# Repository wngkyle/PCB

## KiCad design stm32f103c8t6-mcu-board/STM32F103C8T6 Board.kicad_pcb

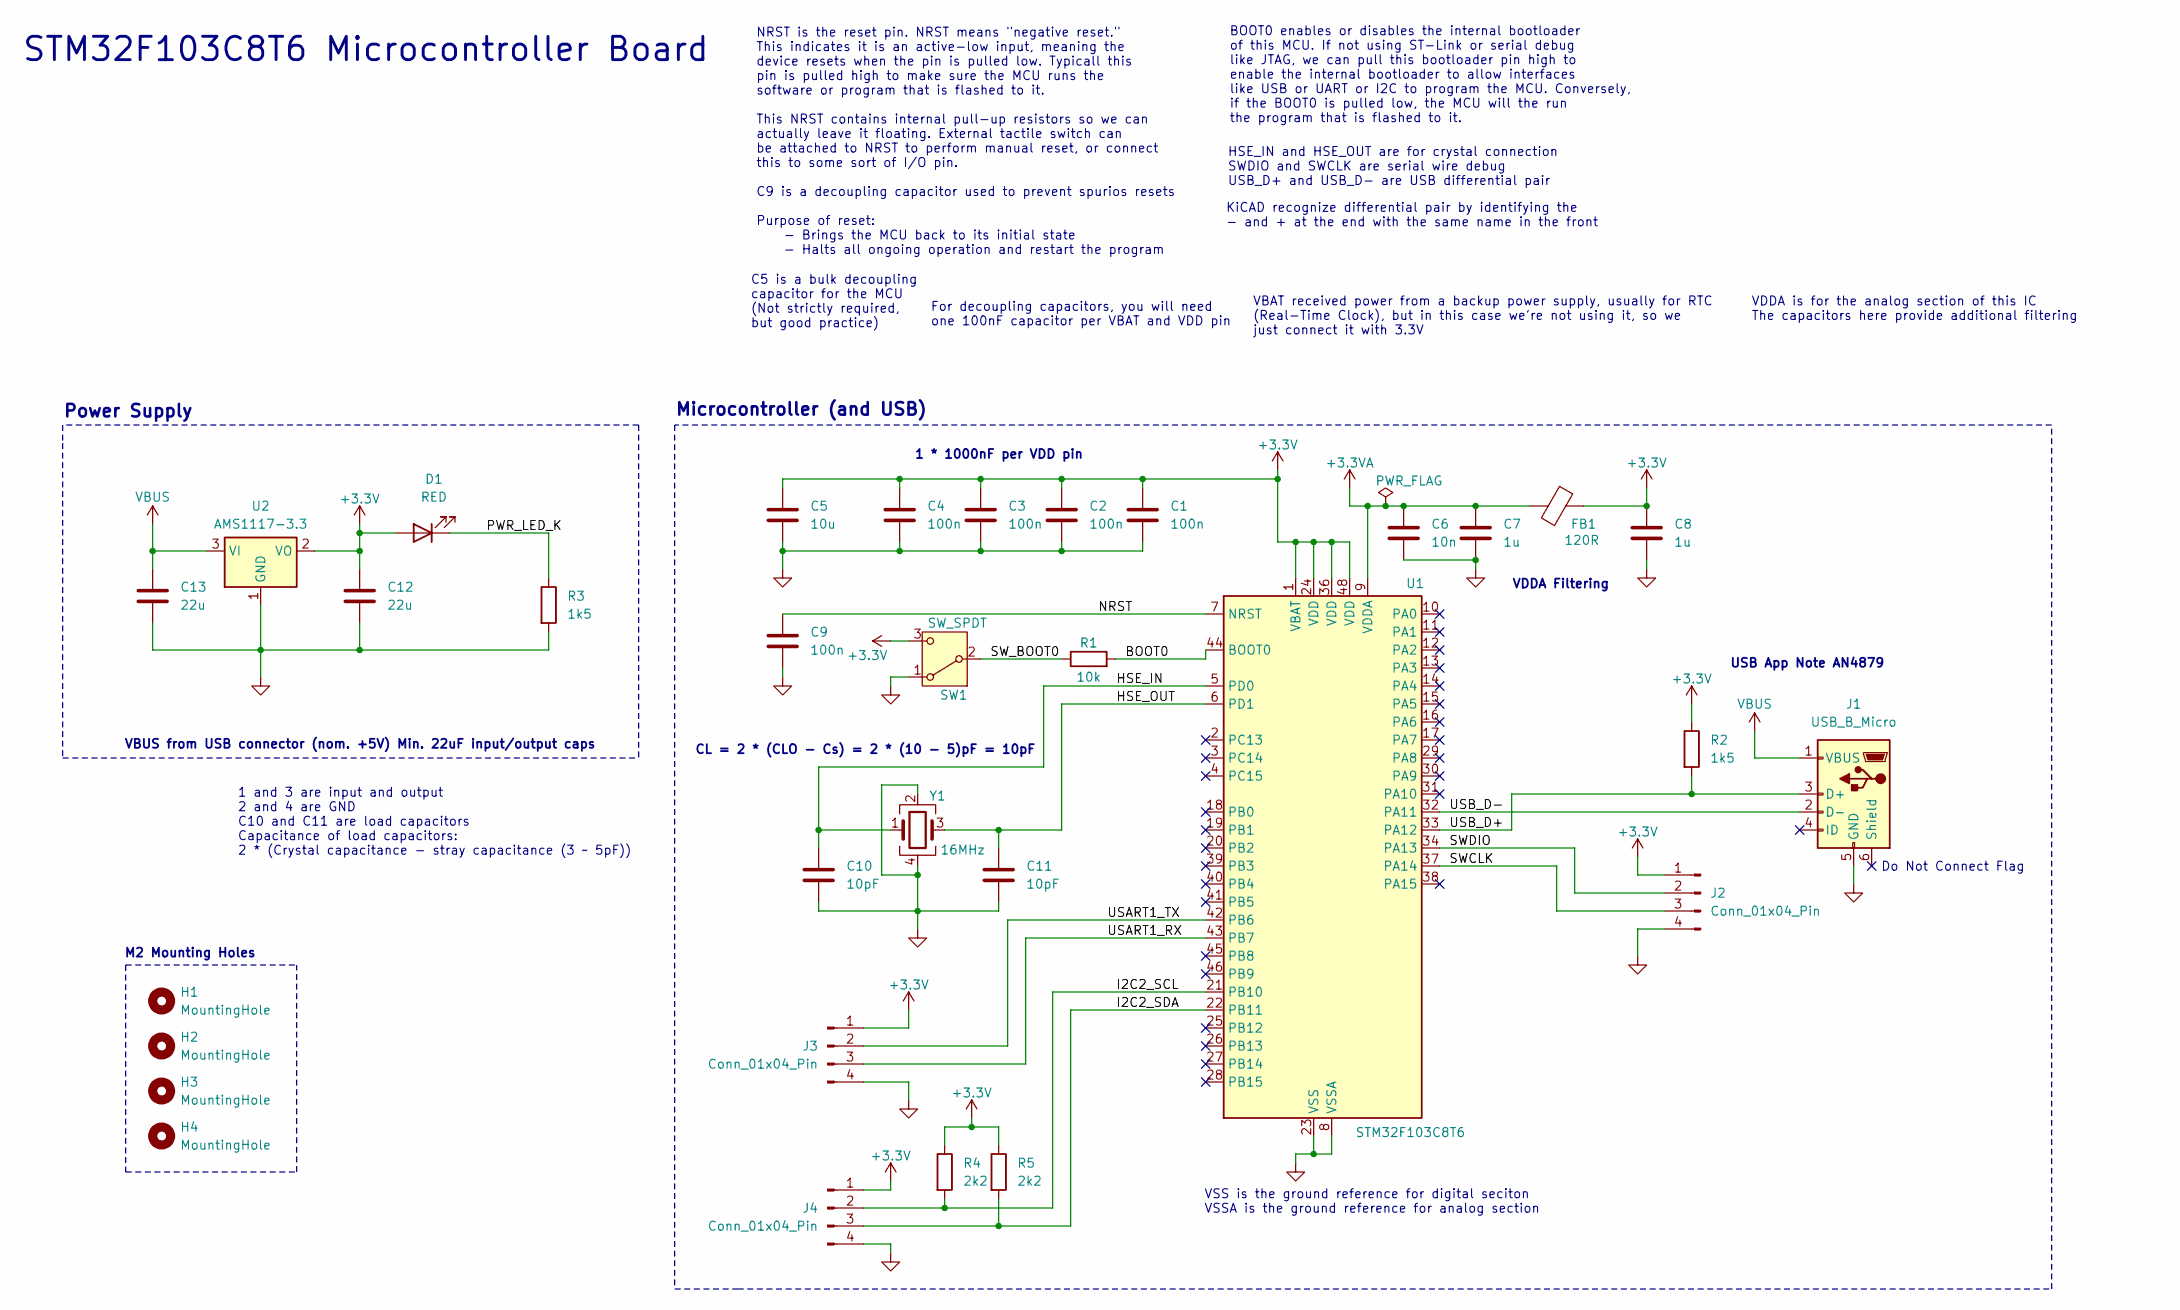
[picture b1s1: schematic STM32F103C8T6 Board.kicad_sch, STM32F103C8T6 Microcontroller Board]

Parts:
C1, C2, C3, C4, C9: 100n; C_0402_1005Metric
C5: 10u; C_0201_0603Metric
C6: 10n; C_0402_1005Metric
C7, C8: 1u; C_0402_1005Metric
C10, C11: 10pF; C_0402_1005Metric
C12, C13: 22u; C_0805_2012Metric
D1: RED; LED_0603_1608Metric
FB1: 120R; L_0603_1608Metric
H1, H2, H3, H4: MountingHole; MountingHole_2.2mm_M2
J1: USB_B_Micro; USB_Micro-B_Wuerth_629105150521
J2, J3, J4: Conn_01x04_Pin; PinHeader_1x04_P2.54mm_Vertical
R1: 10k; R_0402_1005Metric
R2, R3: 1k5; R_0402_1005Metric
R4, R5: 2k2; R_0402_1005Metric
SW1: SW_SPDT; SW_SPDT_PCM12
U1: STM32F103C8T6; LQFP-48_7x7mm_P0.5mm
U2: AMS1117-3.3; SOT-223-3_TabPin2
Y1: 16MHz; Crystal_SMD_3225-4Pin_3.2x2.5mm

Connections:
+3.3V: C1.1, C2.1, C3.1, C4.1, C5.1, C8.1, C12.1, D1.2 (A), FB1.1, J2.1, J3.1, J4.1, R2.1, R4.1, R5.1, SW1.3 (C), U1.1 (VBAT), U1.24 (VDD), U1.36 (VDD), U1.48 (VDD), U2.2 (VO)
+3.3VA: C6.1, C7.1, FB1.2, U1.9 (VDDA)
/BOOT0: R1.2, U1.44 (BOOT0)
/HSE_IN: C10.1, U1.5 (PD0), Y1.1
/HSE_OUT: C11.1, U1.6 (PD1), Y1.3
/I2C2_SCL: J4.2, R4.2, U1.21 (PB10)
/I2C2_SDA: J4.3, R5.2, U1.22 (PB11)
/NRST: C9.1, U1.7 (NRST)
/PWR_LED_K: D1.1 (K), R3.1
/SWCLK: J2.3, U1.37 (PA14)
/SWDIO: J2.2, U1.34 (PA13)
/SW_BOOT0: R1.1, SW1.2 (B)
/USART1_RX: J3.3, U1.43 (PB7)
/USART1_TX: J3.2, U1.42 (PB6)
/USB_D+: J1.3 (D+), R2.2, U1.33 (PA12)
/USB_D-: J1.2 (D-), U1.32 (PA11)
GND: C1.2, C2.2, C3.2, C4.2, C5.2, C6.2, C7.2, C8.2, C9.2, C10.2, C11.2, C12.2, C13.2, J1.5 (GND), J2.4, J3.4, J4.4, R3.2, SW1.1 (A), U1.8 (VSSA), U1.23 (VSS), U1.35 (VSS), U1.47 (VSS), U2.1 (GND), Y1.2, Y1.4
VBUS: C13.1, J1.1 (VBUS), U2.3 (VI)

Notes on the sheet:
BOOT0 enables or disables the internal bootloader of this MCU. If not using ST-Link or serial debug like JTAG, we can pull this bootloader pin high to enable the internal bootloader to allow interfaces like USB or UART or I2C to program the MCU. Conversely, if the BOOT0 is pulled low, the MCU will 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
STM32F103C8T6 Microcontroller Board
Do Not Connect Flag
1 * 1000nF per VDD pin
CL = 2 * (CLO - Cs) = 2 * (10 - 5)pF = 10pF
1 and 3 are input and output 2 and 4 are GND C10 and C11 are load capacitors Capacitance of load capacitors: 2 * (Crystal capacitance - stray capacitance (3 ~ 5pF))
C5 is a bulk decoupling capacitor for the MCU (Not strictly required, but good practice)
VBUS from USB connector (nom. +5V) Min. 22uF input/output caps
KiCAD recognize differential pair by identifying the - and + at the end with the same name in the front
USB App Note AN4879
Power Supply
VBAT received power from a backup power supply, usually for RTC (Real-Time Clock), but in this case we're not using it, so we just connect it with 3.3V
HSE_IN and HSE_OUT are for crystal connection SWDIO and SWCLK are serial wire debug USB_D+ and USB_D- are USB differential pair
VDDA Filtering
VSS is the ground reference for digital seciton VSSA is the ground reference for analog section
For decoupling capacitors, you will need one 100nF capacitor per VBAT and VDD pin
VDDA is for the analog section of this IC The capacitors here provide additional filtering
M2 Mounting Holes
Microcontroller (and USB)
NRST is the reset pin. NRST means "negative reset." This indicates it is an active-low input, meaning the device resets when the pin is pulled low. Typicall this pin is pulled high to make sure the MCU runs the software or program that is flashed to it. This NRST contains internal pull-up resistors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

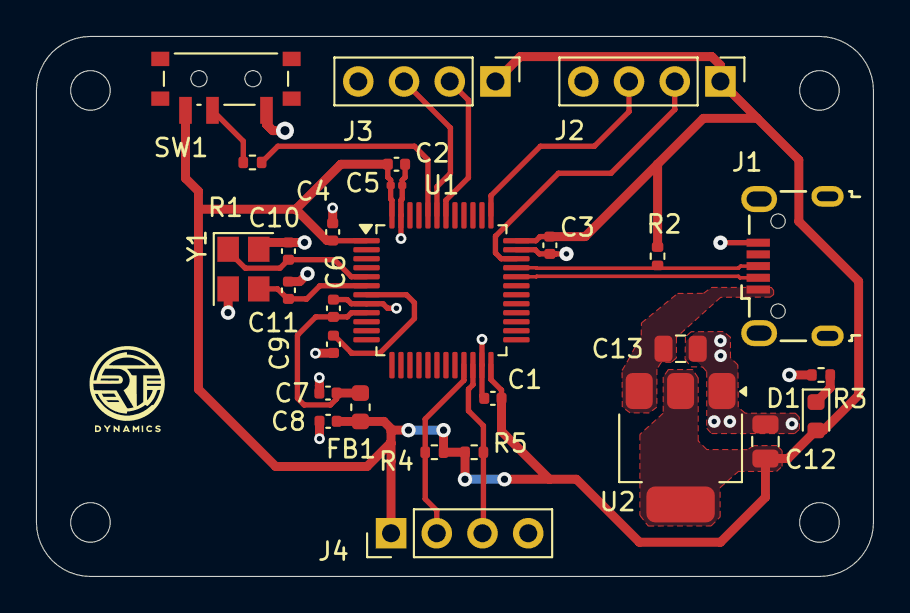
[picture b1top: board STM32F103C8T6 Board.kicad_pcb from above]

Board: 2 copper layers, 46.5 x 30.0 mm, 32 parts (0 on the bottom side), 18 nets.

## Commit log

2025-01-19 add stm32f042t6
2025-01-19 add stm32f103c8t6
